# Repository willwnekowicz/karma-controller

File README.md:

Karma Controller
================
A build-it-yourself 7-button USB controller for controlling Reddit.com through Reddit Enhancement Suite. Karma Controller lets you procrastinate on Reddit more productively. Its 7 buttons are used to up vote, down vote, select posts, toggle images, and open & close comment tabs.

More at http://karmacontroller.com/

The files here include a board layout and schematic, as well as the controller's arduino code.

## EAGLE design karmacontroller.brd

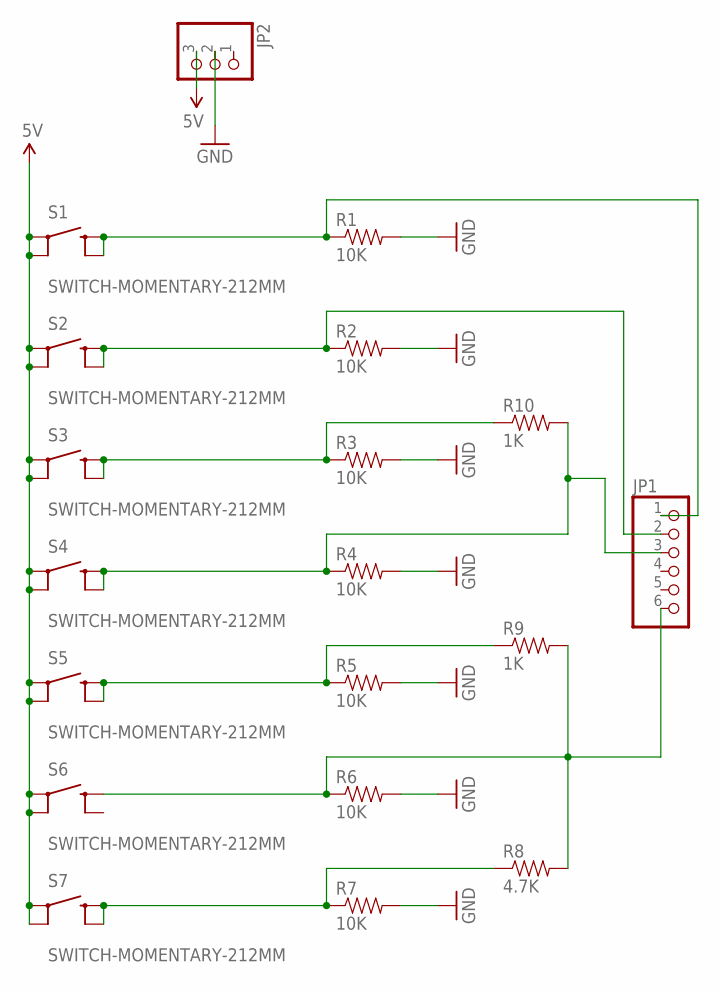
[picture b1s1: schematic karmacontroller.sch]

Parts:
JP1: PINHD-1X6; 1X06
JP2: PINHD-1X3; 1X03
R1, R2, R3, R4, R5, R6, R7: 10K; AXIAL-0.3
R8: 4.7K; AXIAL-0.3
R9, R10: 1K; AXIAL-0.3
S1, S2, S3, S4, S5, S6, S7: SWITCH-MOMENTARY-212MM; TACTILE-PTH-12MM

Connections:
5V: JP2.3, S1.1, S1.2 (1'), S2.1, S2.2 (1'), S3.1, S3.2 (1'), S4.1, S4.2 (1'), S5.1, S5.2 (1'), S6.1, S6.2 (1'), S7.1, S7.2 (1')
DOWN: R7.P$1 (1), R8.P$1 (1), S7.3 (2), S7.4 (2')
GND: JP2.2, R1.P$2 (2), R2.P$2 (2), R3.P$2 (2), R4.P$2 (2), R5.P$2 (2), R6.P$2 (2), R7.P$2 (2)
unnamed: JP1.2, R2.P$1 (1), S2.3 (2), S2.4 (2')
unnamed: JP1.1, R1.P$1 (1), S1.3 (2), S1.4 (2')
unnamed: JP1.3, R4.P$1 (1), R10.P$2 (2), S4.3 (2), S4.4 (2')
unnamed: R5.P$1 (1), R9.P$1 (1), S5.3 (2), S5.4 (2')
unnamed: JP1.6, R6.P$1 (1), R8.P$2 (2), R9.P$2 (2), S6.3 (2)
unnamed: R3.P$1 (1), R10.P$1 (1), S3.3 (2), S3.4 (2')

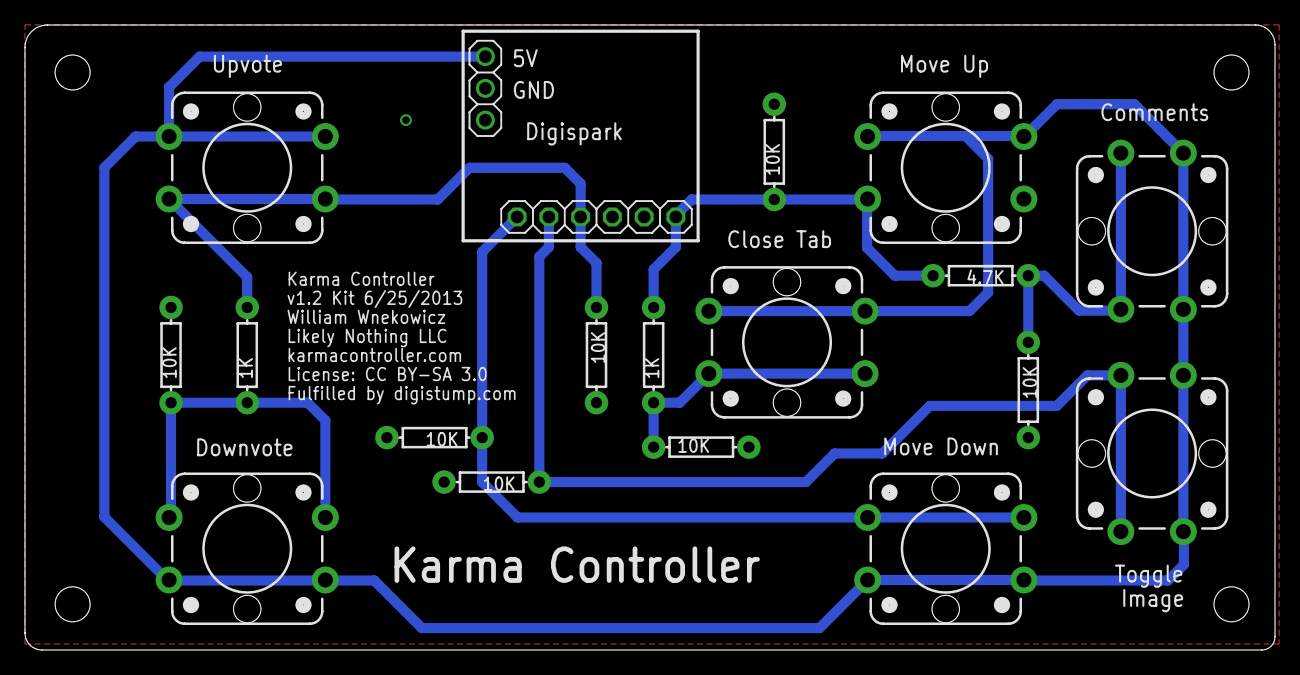
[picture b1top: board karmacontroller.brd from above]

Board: 2 copper layers, 100.0 x 50.0 mm, 19 parts (0 on the bottom side), 9 nets.

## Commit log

2013-04-16 Karma Controller v1.0 Initial Commit
2013-04-18 v1.1 for first production PCB print
2013-04-18 Added DigiSpark Arduino code
2013-05-29 Prepared for fabrication (v1.1)
2013-07-16 Upgraded board and software
    - I changed all the resistors to the Sparkfun AXIAL-0.3 and rerouted
    everything.
    - I changed the mask limit to 25mil.
    - I moved the "Karma Controller" text over to the left.
    - I hid the tOrigins layer. These are the crosshairs.
    - I updated the date to 6/25/2013

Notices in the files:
karmacontroller.brd:
License: CC BY-SA 3.0
parts and their libraries:
SparkFun-Electromechanical: Licensing: CC v3.0 Share-Alike You are welcome to use this library for commercial purposes.
